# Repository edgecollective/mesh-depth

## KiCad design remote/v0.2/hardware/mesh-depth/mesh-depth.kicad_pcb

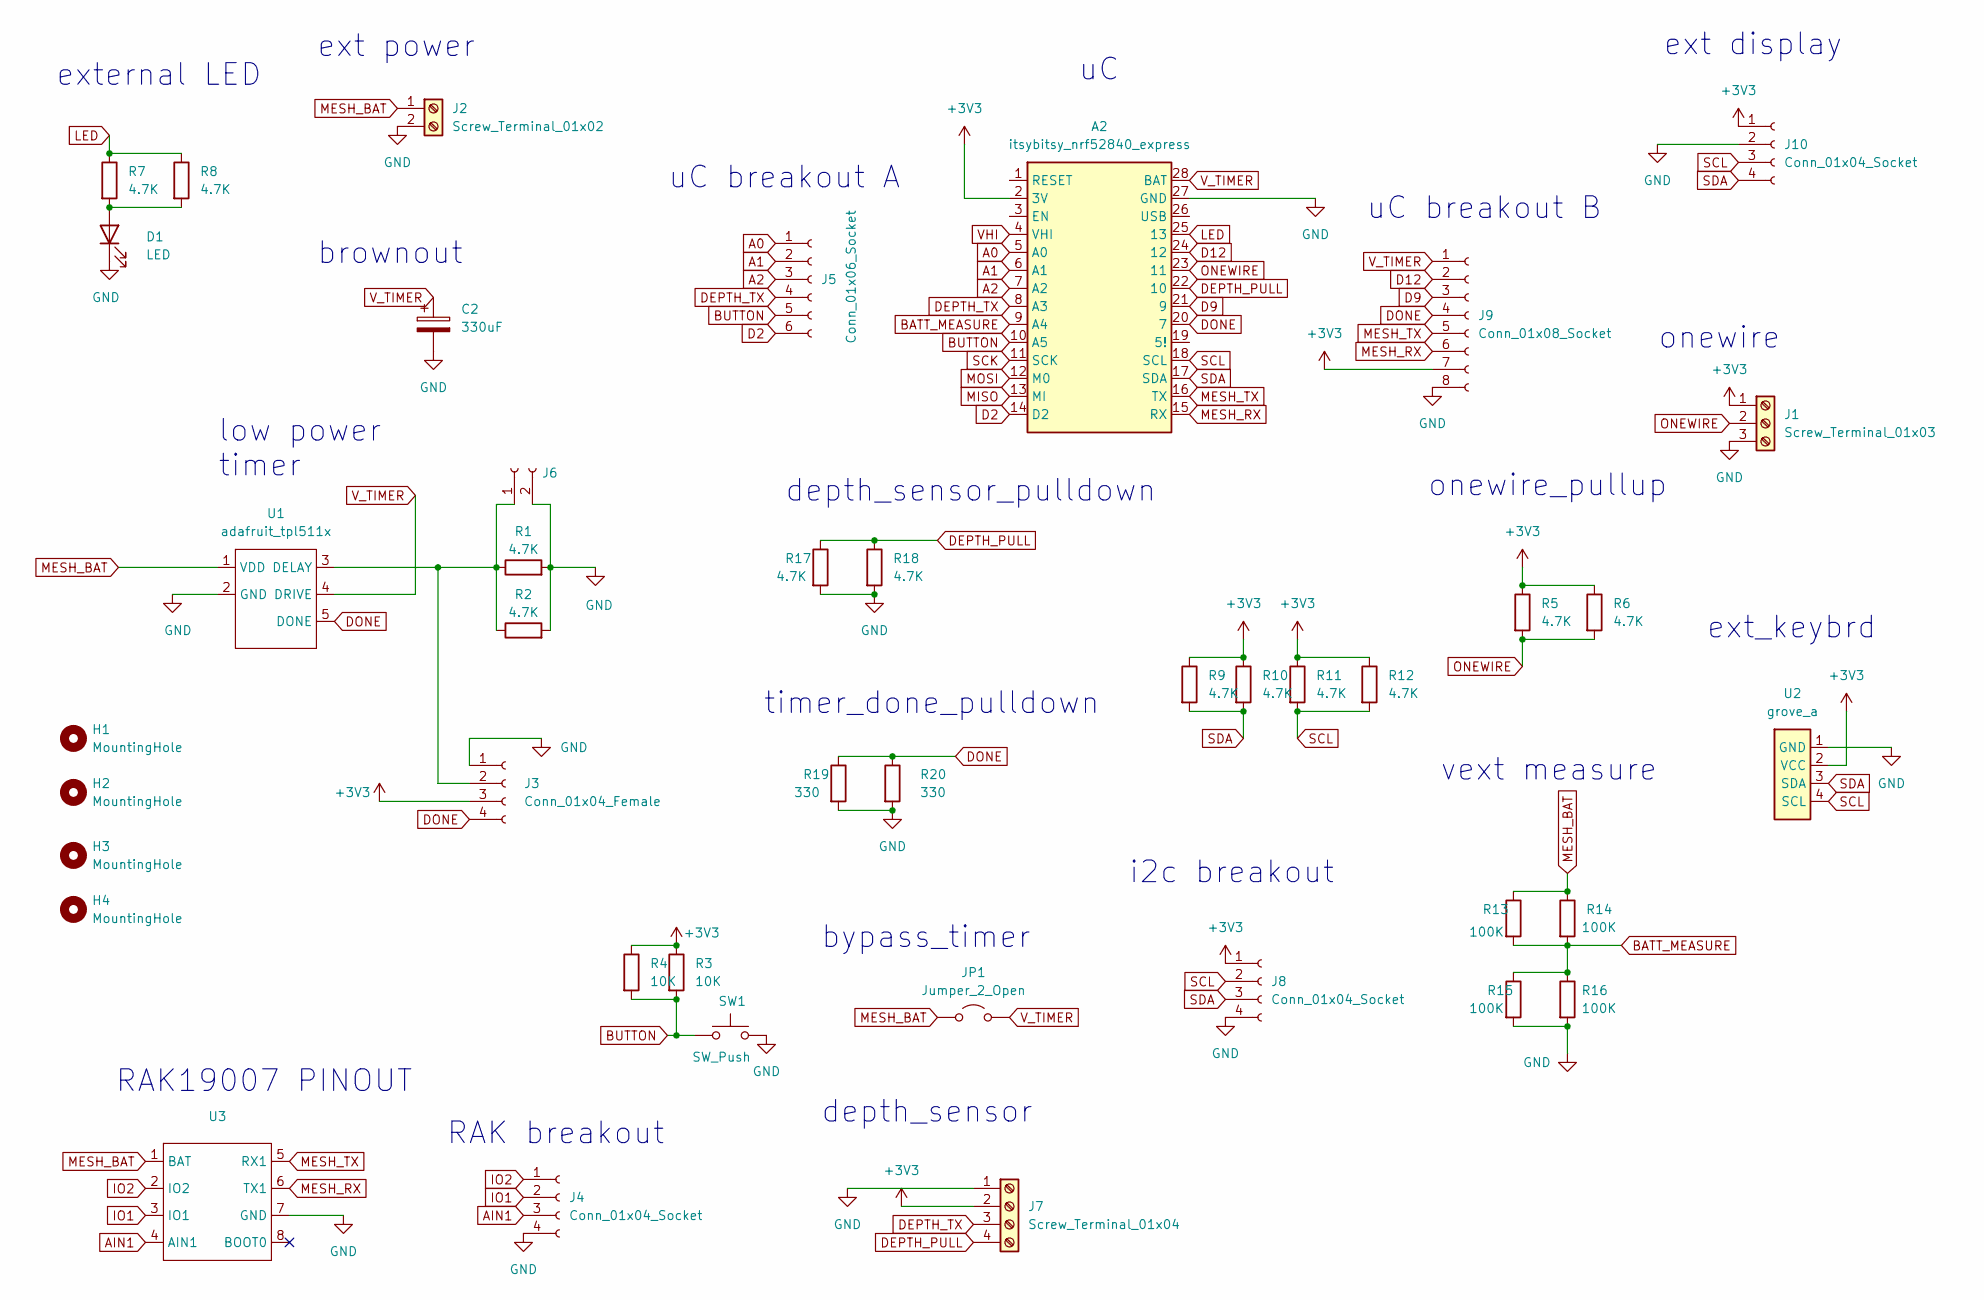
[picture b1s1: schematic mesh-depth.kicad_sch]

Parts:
A2: itsybitsy_nrf52840_express; itsybitsy
C2: 330uF; CP_Radial_D5.0mm_P2.00mm
D1: LED; LED_D5.0mm
H1, H2, H3, H4: MountingHole; MountingHole_3.2mm_M3
J1: Screw_Terminal_01x03; TerminalBlock_Phoenix_MKDS-1,5-3_1x03_P5.00mm_Horizontal
J2: Screw_Terminal_01x02; TerminalBlock_Phoenix_MKDS-1,5-2_1x02_P5.00mm_Horizontal
J3: Conn_01x04_Female; PinSocket_1x04_P2.54mm_Vertical
J4, J8: Conn_01x04_Socket; PinHeader_1x04_P2.54mm_Vertical
J5: Conn_01x06_Socket; PinHeader_1x06_P2.54mm_Vertical
J6: Conn_01x02_Socket; PinSocket_1x02_P2.54mm_Vertical
J7: Screw_Terminal_01x04; TerminalBlock_Phoenix_MKDS-1,5-4_1x04_P5.00mm_Horizontal
J9: Conn_01x08_Socket; PinHeader_1x08_P2.54mm_Vertical
J10: Conn_01x04_Socket; ssd1306_a
JP1: Jumper_2_Open; SolderJumper-2_P1.3mm_Open_Pad1.0x1.5mm
R1, R5, R8, R10, R11, R18: 4.7K; R_0603_1608Metric_Pad0.98x0.95mm_HandSolder
R2, R6, R7, R9, R12, R17: 4.7K; R_Axial_DIN0204_L3.6mm_D1.6mm_P7.62mm_Horizontal
R3: 10K; R_0603_1608Metric_Pad0.98x0.95mm_HandSolder
R4: 10K; R_Axial_DIN0204_L3.6mm_D1.6mm_P7.62mm_Horizontal
R13, R15: 100K; R_Axial_DIN0204_L3.6mm_D1.6mm_P7.62mm_Horizontal
R14, R16: 100K; R_0603_1608Metric_Pad0.98x0.95mm_HandSolder
R19: 330; R_Axial_DIN0204_L3.6mm_D1.6mm_P7.62mm_Horizontal
R20: 330; R_0603_1608Metric_Pad0.98x0.95mm_HandSolder
SW1: SW_Push; SW_PUSH_6mm
U1: adafruit_tpl511x
U2: grove_a
U3: rak19007

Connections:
+3V3: A2.2 (3V), J1.1, J3.3, J7.2, J8.1, J9.7, J10.1, R3.1, R4.1, R5.1, R6.1, R9.1, R10.1, R11.1, R12.1, U2.2 (VCC)
A0: A2.5 (A0), J5.1
A1: A2.6 (A1), J5.2
A2: A2.7 (A2), J5.3
AIN1: J4.3, U3.4 (AIN1)
BATT_MEASURE: A2.9 (A4), R13.2, R14.2, R15.1, R16.1
BUTTON: A2.10 (A5), J5.5, R3.2, R4.2, SW1.1
D2: A2.14 (D2), J5.6
D9: A2.21 (9), J9.3
D12: A2.24 (12), J9.2
DEPTH_PULL: A2.22 (10), J7.4, R17.1, R18.1
DEPTH_TX: A2.8 (A3), J5.4, J7.3
DONE: A2.20 (7), J3.4, J9.4, R19.1, R20.1, U1.5 (DONE)
GND: A2.27 (GND), C2.2, D1.1 (K), J1.3, J2.2, J3.1, J4.4, J6.2, J7.1, J8.4, J9.8, J10.2, R1.2, R2.2, R15.2, R16.2, R17.2, R18.2, R19.2, R20.2, SW1.2, U1.2 (GND), U2.1 (GND), U3.7 (GND)
IO1: J4.2, U3.3 (IO1)
IO2: J4.1, U3.2 (IO2)
LED: A2.25 (13), R7.1, R8.1
MESH_BAT: J2.1, JP1.1 (A), R13.1, R14.1, U1.1 (VDD), U3.1 (BAT)
MESH_RX: A2.15 (RX), J9.6, U3.6 (TX1)
MESH_TX: A2.16 (TX), J9.5, U3.5 (RX1)
MISO: A2.13 (MI)
MOSI: A2.12 (M0)
unnamed: D1.2 (A), R7.2, R8.2
unnamed: J3.2, J6.1, R1.1, R2.1, U1.3 (DELAY)
ONEWIRE: A2.23 (11), J1.2, R5.2, R6.2
SCK: A2.11 (SCK)
SCL: A2.18 (SCL), J8.2, J10.3, R11.2, R12.2, U2.4 (SCL)
SDA: A2.17 (SDA), J8.3, J10.4, R9.2, R10.2, U2.3 (SDA)
VHI: A2.4 (VHI)
V_TIMER: A2.28 (BAT), C2.1, J9.1, JP1.2 (B), U1.4 (DRIVE)

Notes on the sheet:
uC breakout A
bypass_timer
brownout
depth_sensor_pulldown
vext measure
onewire
timer_done_pulldown
ext_keybrd
onewire_pullup
uC breakout B
external LED
depth_sensor
RAK breakout
low power timer
ext power
i2c breakout
ext display
RAK19007 PINOUT

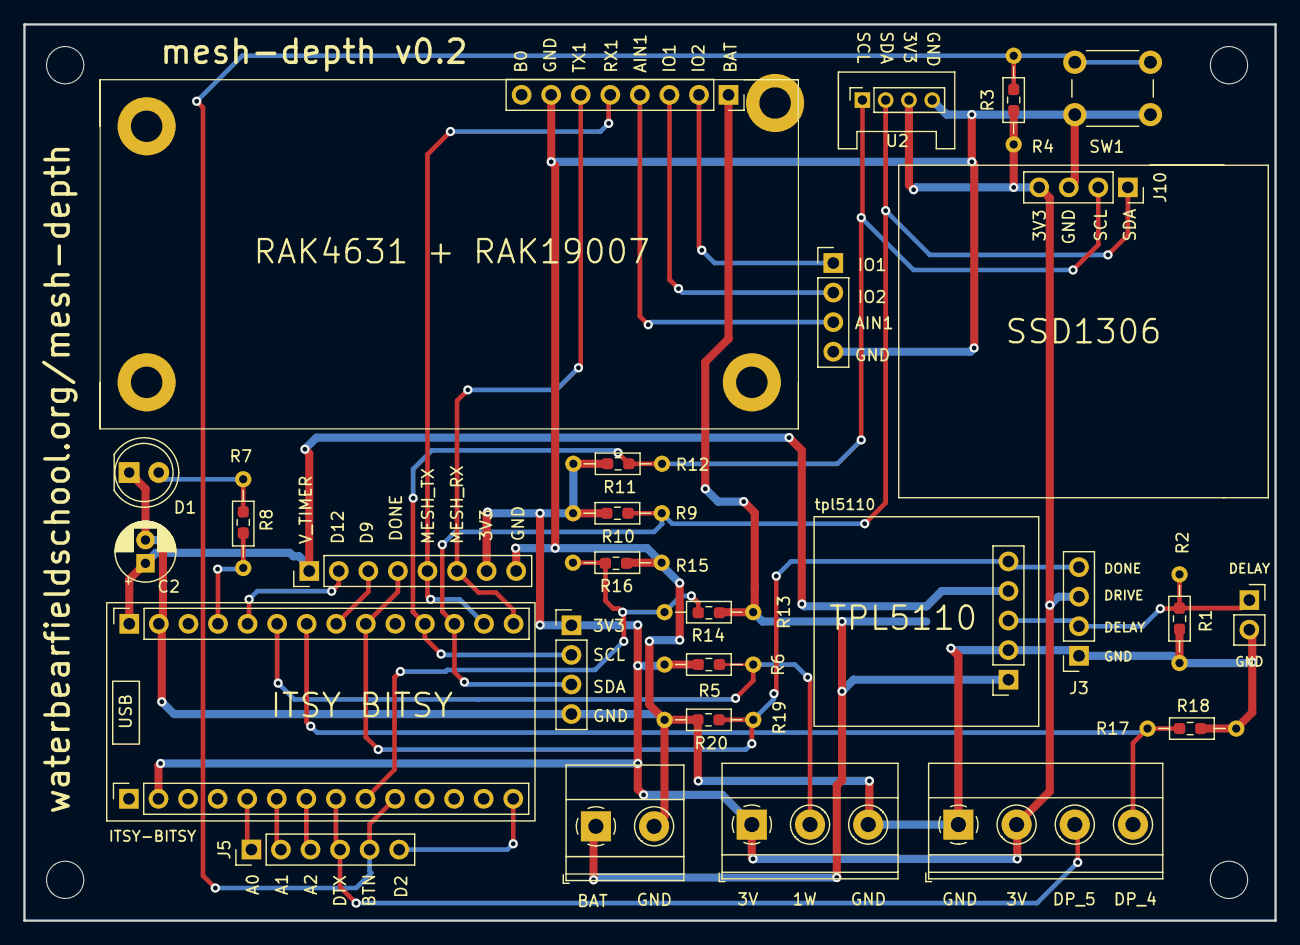
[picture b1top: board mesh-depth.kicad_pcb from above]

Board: 2 copper layers, 107.5 x 77.0 mm, 42 parts (1 on the bottom side), 26 nets.

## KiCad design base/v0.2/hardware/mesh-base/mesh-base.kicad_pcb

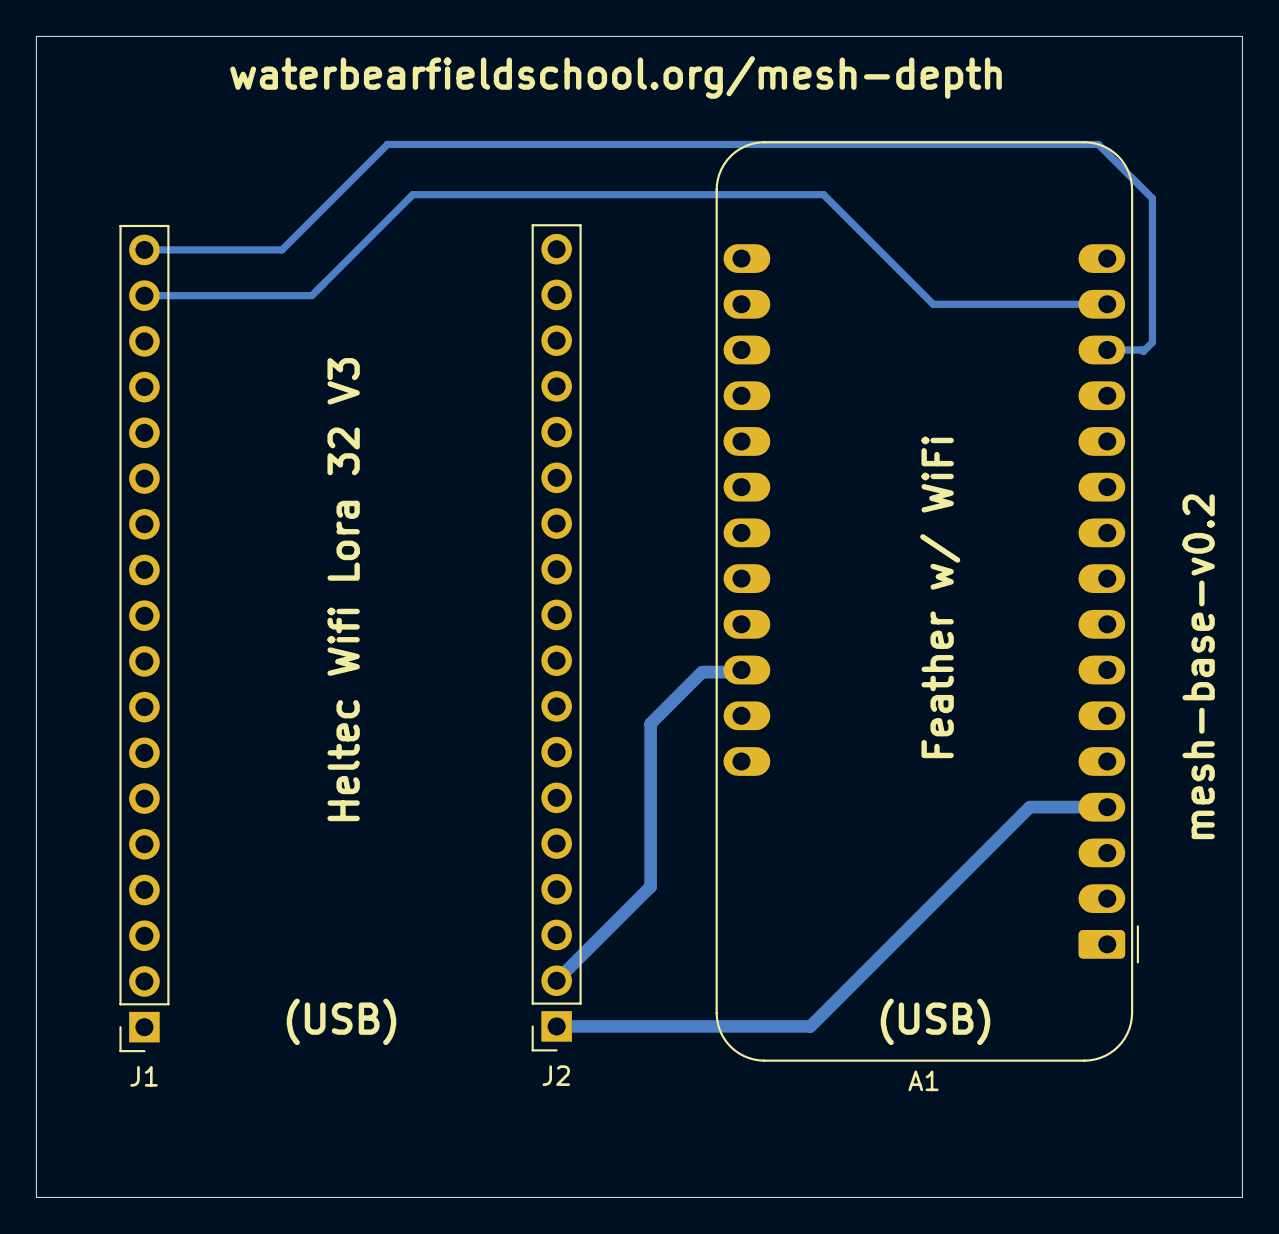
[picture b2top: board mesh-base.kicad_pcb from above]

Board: 2 copper layers, 67.0 x 64.5 mm, 3 parts (0 on the bottom side), 4 nets.

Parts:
A1: Adafruit_Feather_Generic; Adafruit_Feather
J1, J2: Conn_01x18_Socket; PinSocket_1x18_P2.54mm_Vertical

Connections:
GND: A1.4 (GND), J2.1
GPIO6: A1.15 (TX), J1.17
GPIO7: A1.14 (RX), J1.18
VUSB: A1.26 (USB), J2.2
